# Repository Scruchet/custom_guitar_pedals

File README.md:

# Custom Guitar Pedals

## Introduction
Since I started learning how to play the electric bass and guitar, and while learning new songs, I discovered effect pedals. They change the sound of the instrument by adding more texture and character. Many different types of pedals exist, and I wanted to understand how they work.

My research is mainly based on a book that I highly recommend: *Electronics for Guitarists* (third edition).

## Project Structure
This repository contains all the files needed to create your own guitar pedals, from electronic design to 3D models and circuit simulation.

The main directory is divided into three subdirectories:
- **mechanical**: Fusion 360 and STEP files for the enclosure
- **pcb**: KiCad projects with an HTML-generated BOM for easier assembly
- **simulation**: LTSpice projects used to design and validate the two main circuits

## Effects
The project currently includes two pedals:
- A clipping pedal
- A fuzz face–style pedal

## Assembly
To assemble the pedals, you will need several components. All passive and active components are listed in the BOM available at `pcb/bom/ibom.html`.

You can 3D print the enclosure, but I do not really recommend it. A pedal needs to be solid and reliable, especially for stage use.  
I bought aluminum enclosures from AliExpress and adapted the designs to fit the available space. The quality is not the best, but this is a DIY project after all.

You will need:
- Two 6.35 mm jack connectors (input and output)
- One DC jack for the power supply
- One LED with its current-limiting resistor
- One 3PDT guitar footswitch

All the components I used are listed in the `components.txt` file.

## Results

`images/result.jpg`

## Project Status

Tested, need pictures for the readme

## License
All hardware designs, schematics, PCB layouts, and mechanical files in this repository
are released under the CERN Open Hardware Licence v2 – Permissive (CERN-OHL-P).

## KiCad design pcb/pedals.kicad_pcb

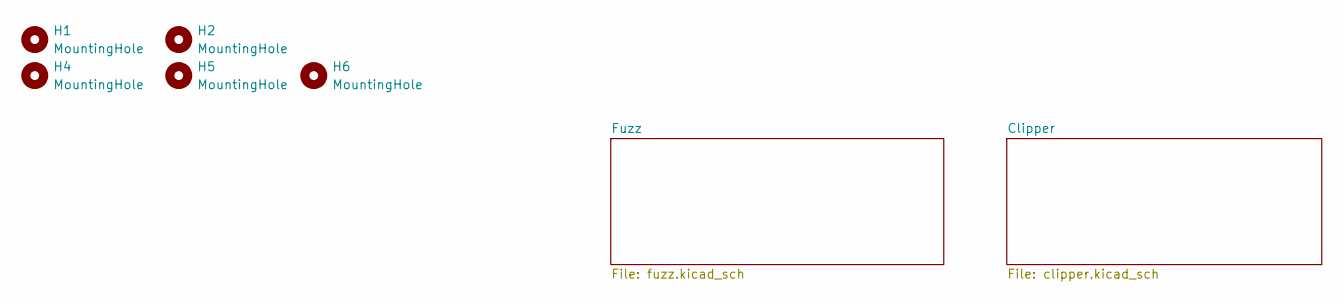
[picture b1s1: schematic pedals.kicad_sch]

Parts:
H1, H2, H4, H5, H6: MountingHole; mouse-bite-2mm-slot

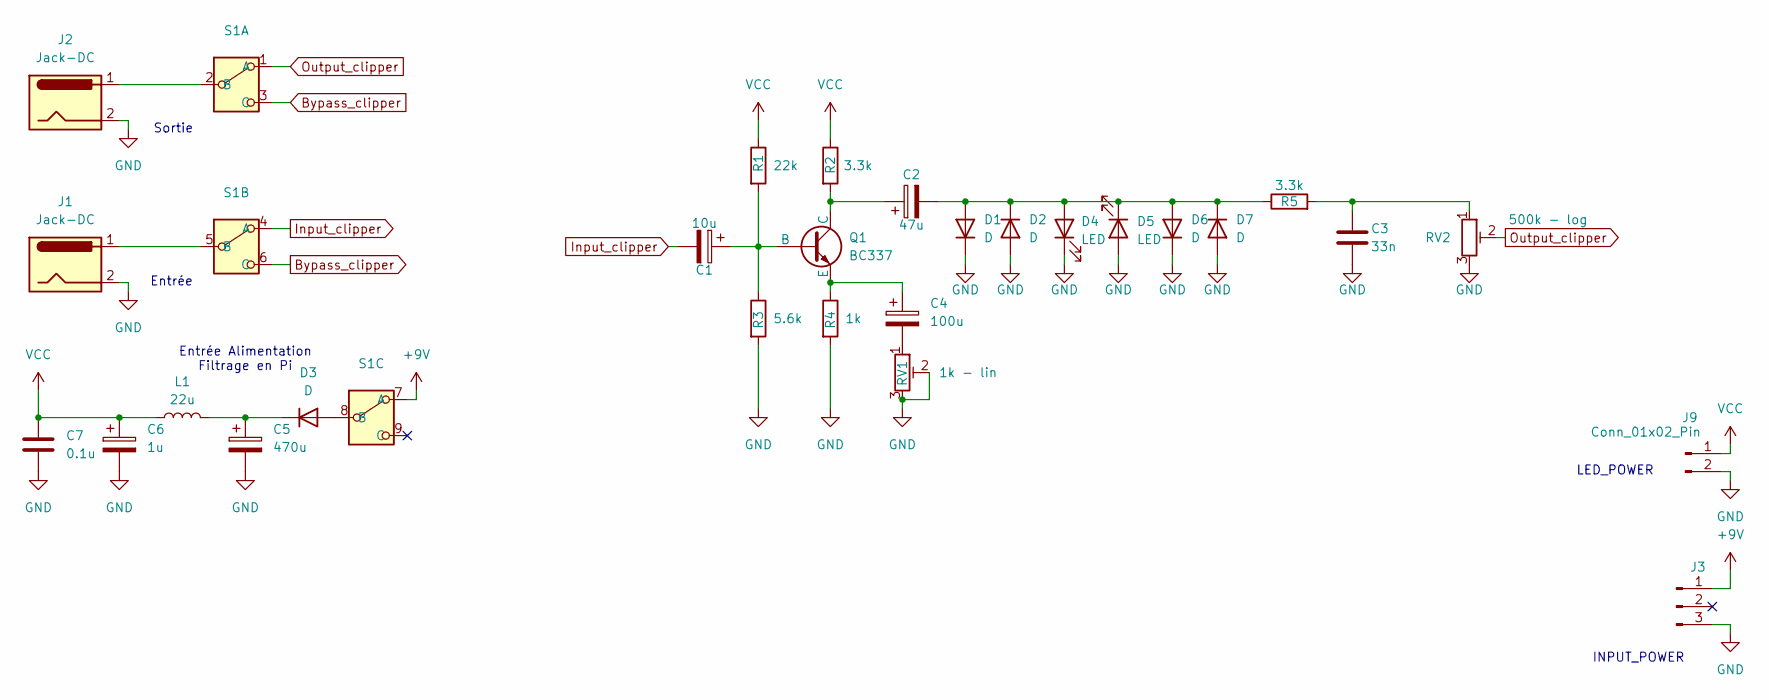
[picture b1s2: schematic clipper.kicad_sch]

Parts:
C1: 10u; CP_Radial_D4.0mm_P2.00mm
C2: 47u; CP_Radial_D5.0mm_P2.00mm
C3: 33n; CAP_C322_KEM
C4: 100u; CP_Radial_D5.0mm_P2.00mm
C5: 470u; CP_Radial_D8.0mm_P3.80mm
C6: 1u; CP_Radial_D5.0mm_P2.00mm
C7: 0.1u; CAP_C322_KEM
D1, D2, D3: D; D_DO-41_SOD81_P10.16mm_Horizontal
D4, D5: LED; LED_D3.0mm
D6, D7: D; D_A-405_P10.16mm_Horizontal
J1, J2: Jack-DC; PinHeader_1x02_P2.54mm_Vertical
J3: Conn_01x03_Pin; PinHeader_1x03_P2.54mm_Vertical
J9: Conn_01x02_Pin; PinHeader_1x02_P2.54mm_Vertical
L1: 22u; L_Axial_L9.5mm_D4.0mm_P12.70mm_Horizontal_Fastron_SMCC
Q1: BC337; TO-92_HandSolder
R1: 22k; R_Axial_DIN0207_L6.3mm_D2.5mm_P10.16mm_Horizontal
R2, R5: 3.3k; R_Axial_DIN0207_L6.3mm_D2.5mm_P10.16mm_Horizontal
R3: 5.6k; R_Axial_DIN0207_L6.3mm_D2.5mm_P10.16mm_Horizontal
R4: 1k; R_Axial_DIN0207_L6.3mm_D2.5mm_P10.16mm_Horizontal
RV1: 1k - lin; PinHeader_1x03_P2.54mm_Vertical
RV2: 500k - log; PinHeader_1x03_P2.54mm_Vertical
S1: Switch_Principal

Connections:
+9V: J3.1, S1.7 (A)
Bypass_clipper: S1.3 (C), S1.6 (C)
GND: C3.2, C5.2, C6.2, C7.2, D1.1 (K), D2.2 (A), D4.1 (K), D5.2 (A), D6.1 (K), D7.2 (A), J1.2, J2.2, J3.3, J9.2, R3.2, R4.2, RV1.2, RV1.3, RV2.3
Input_clipper: C1.2, S1.4 (A)
unnamed: C3.1, R5.2, RV2.1
unnamed: C4.2, RV1.1
unnamed: C2.2, D1.2 (A), D2.1 (K), D4.2 (A), D5.1 (K), D6.2 (A), D7.1 (K), R5.1
unnamed: D3.2 (A), S1.8 (B)
unnamed: C5.1, D3.1 (K), L1.2
unnamed: C1.1, Q1.2 (B), R1.2, R3.1
unnamed: C2.1, Q1.1 (C), R2.2
unnamed: C4.1, Q1.3 (E), R4.1
unnamed: J2.1, S1.2 (B)
unnamed: J1.1, S1.5 (B)
Output_clipper: RV2.2, S1.1 (A)
VCC: C6.1, C7.1, J9.1, L1.1, R1.1, R2.1

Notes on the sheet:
INPUT_POWER
Entrée Alimentation Filtrage en Pi
Entrée
LED_POWER
Sortie

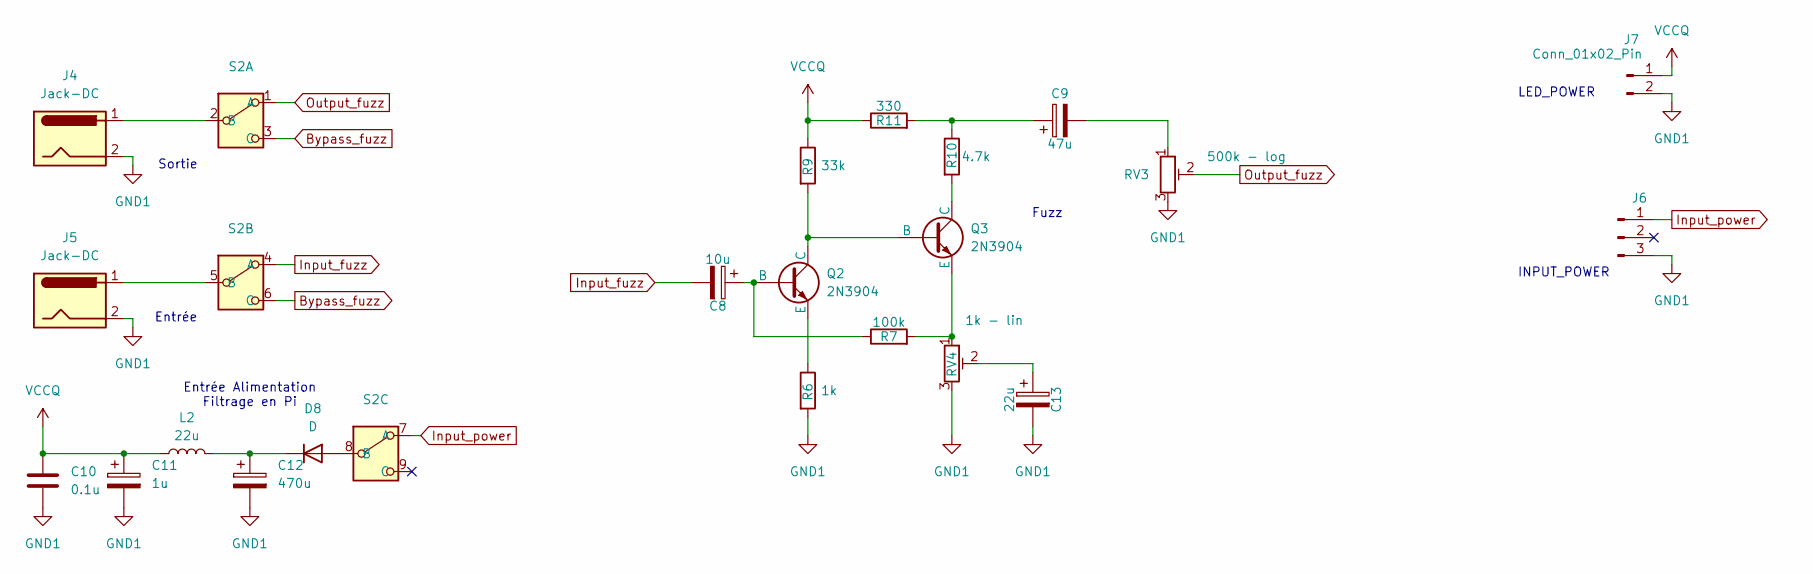
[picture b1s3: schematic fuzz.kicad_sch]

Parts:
C8: 10u; CP_Radial_D4.0mm_P2.00mm
C9: 47u; CP_Radial_D5.0mm_P2.00mm
C10: 0.1u; CAP_C322_KEM
C11: 1u; CP_Radial_D5.0mm_P2.00mm
C12: 470u; CP_Radial_D8.0mm_P3.80mm
C13: 22u; CP_Radial_D4.0mm_P2.00mm
D8: D; D_DO-41_SOD81_P10.16mm_Horizontal
J4, J5: Jack-DC; PinHeader_1x02_P2.54mm_Vertical
J6: Conn_01x03_Pin; PinHeader_1x03_P2.54mm_Vertical
J7: Conn_01x02_Pin; PinHeader_1x02_P2.54mm_Vertical
L2: 22u; L_Axial_L9.5mm_D4.0mm_P12.70mm_Horizontal_Fastron_SMCC
Q2, Q3: 2N3904
R6: 1k; R_Axial_DIN0207_L6.3mm_D2.5mm_P10.16mm_Horizontal
R7: 100k; R_Axial_DIN0207_L6.3mm_D2.5mm_P10.16mm_Horizontal
R9: 33k; R_Axial_DIN0207_L6.3mm_D2.5mm_P10.16mm_Horizontal
R10: 4.7k; R_Axial_DIN0207_L6.3mm_D2.5mm_P10.16mm_Horizontal
R11: 330; R_Axial_DIN0207_L6.3mm_D2.5mm_P10.16mm_Horizontal
RV3: 500k - log; PinHeader_1x03_P2.54mm_Vertical
RV4: 1k - lin; PinHeader_1x03_P2.54mm_Vertical
S2: Switch_Principal

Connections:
Bypass_fuzz: S2.3 (C), S2.6 (C)
GND1: C10.2, C11.2, C12.2, C13.2, J4.2, J5.2, J6.3, J7.2, R6.2, RV3.3, RV4.3
Input_fuzz: C8.2, S2.4 (A)
Input_power: J6.1, S2.7 (A)
unnamed: C9.1, R10.1, R11.2
unnamed: C9.2, RV3.1
unnamed: C13.1, RV4.2
unnamed: D8.2 (A), S2.8 (B)
unnamed: C12.1, D8.1 (K), L2.2
unnamed: C8.1, Q2.2 (B), R7.1
unnamed: Q2.1 (C), Q3.2 (B), R9.2
unnamed: Q2.3 (E), R6.1
unnamed: Q3.1 (C), R10.2
unnamed: Q3.3 (E), R7.2, RV4.1
unnamed: J4.1, S2.2 (B)
unnamed: J5.1, S2.5 (B)
Output_fuzz: RV3.2, S2.1 (A)
VCCQ: C10.1, C11.1, J7.1, L2.1, R9.1, R11.1

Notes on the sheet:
Sortie
LED_POWER
Fuzz
Entrée Alimentation Filtrage en Pi
Entrée
INPUT_POWER

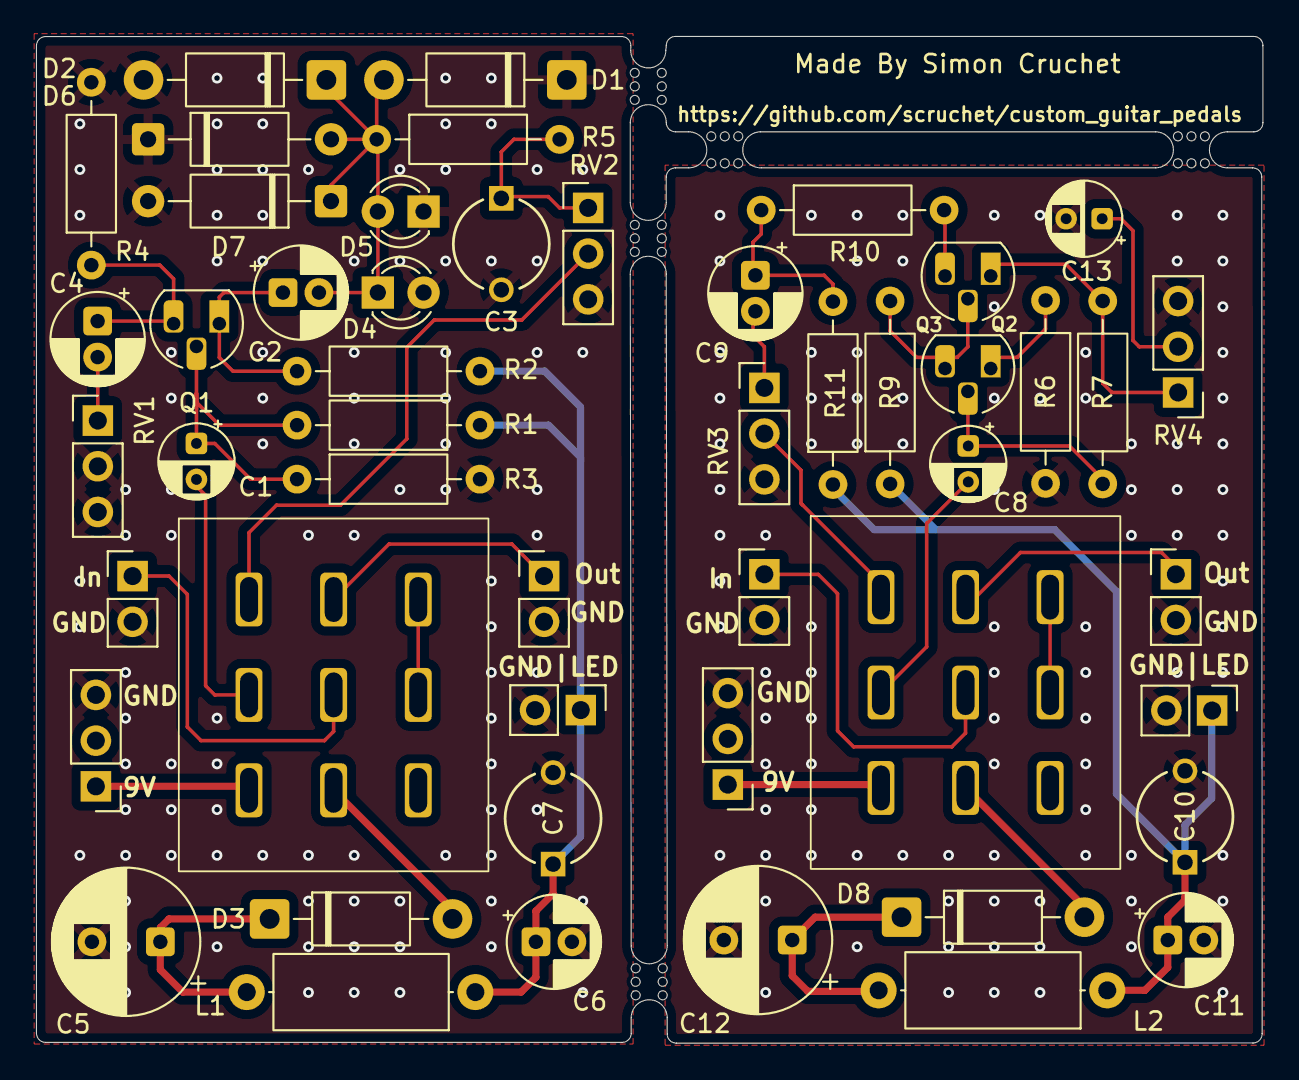
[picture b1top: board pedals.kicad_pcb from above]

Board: 2 copper layers, 68.1 x 55.9 mm, 55 parts (0 on the bottom side), 34 nets.

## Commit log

2025-12-16 Remove duplicate header from README.md
2025-12-16 pcb added; .gitignore added
2025-12-16 modification folder name
2025-12-16 .gitignore modification
2025-12-16 gerber excluded from git
2025-12-16 adding simulation & mechanical files
2026-01-19 Enhance README with project details and instructions
    Added detailed project information including structure, effects, assembly instructions, and licensing.
2026-01-19 adding componants file and creating images directory
